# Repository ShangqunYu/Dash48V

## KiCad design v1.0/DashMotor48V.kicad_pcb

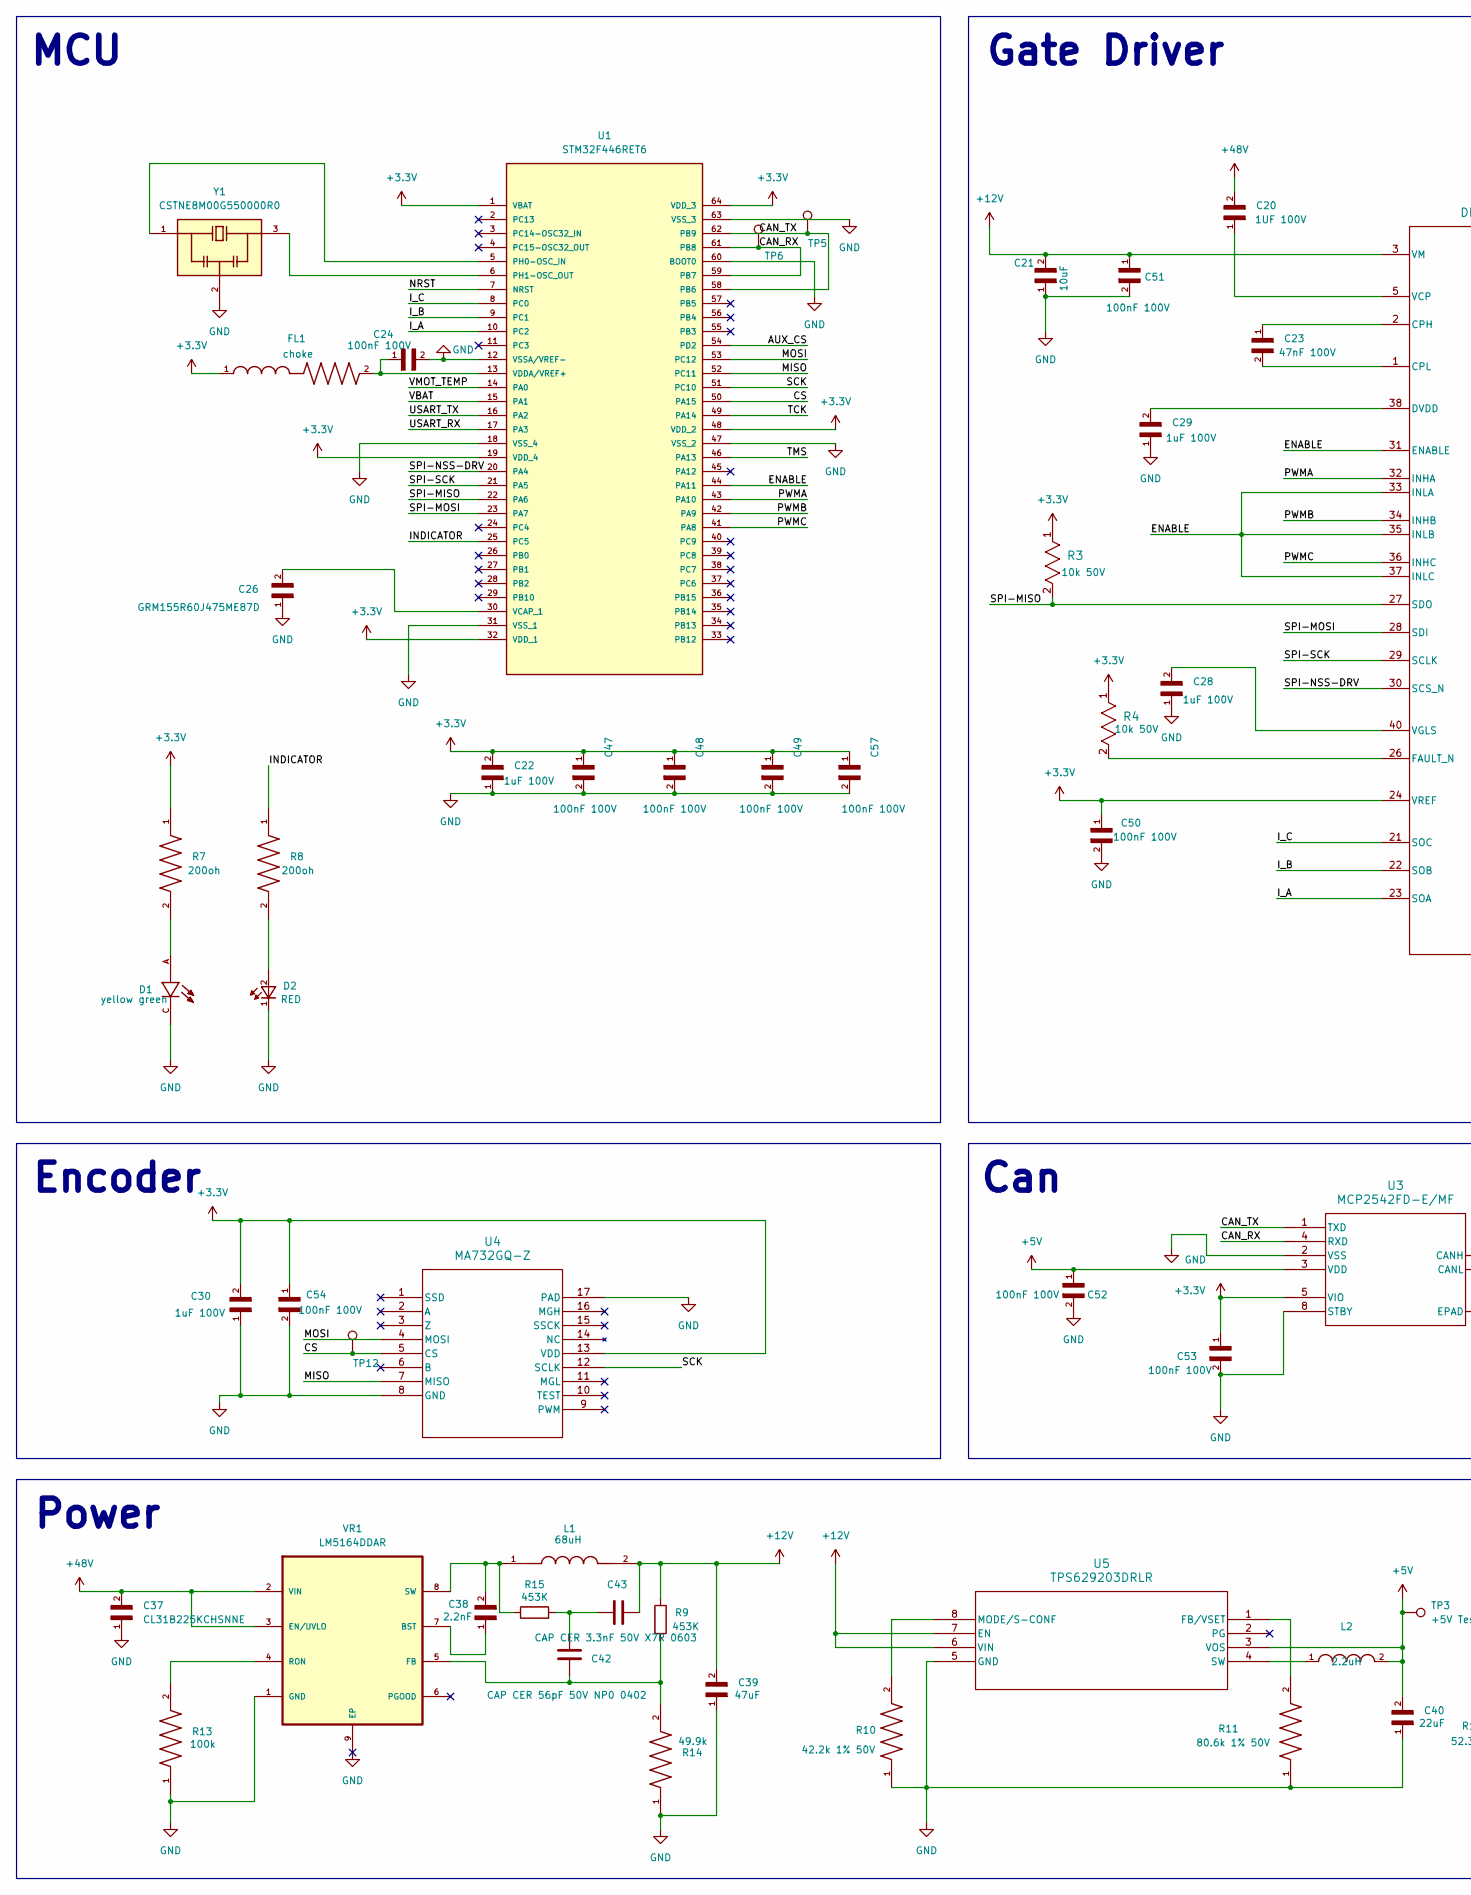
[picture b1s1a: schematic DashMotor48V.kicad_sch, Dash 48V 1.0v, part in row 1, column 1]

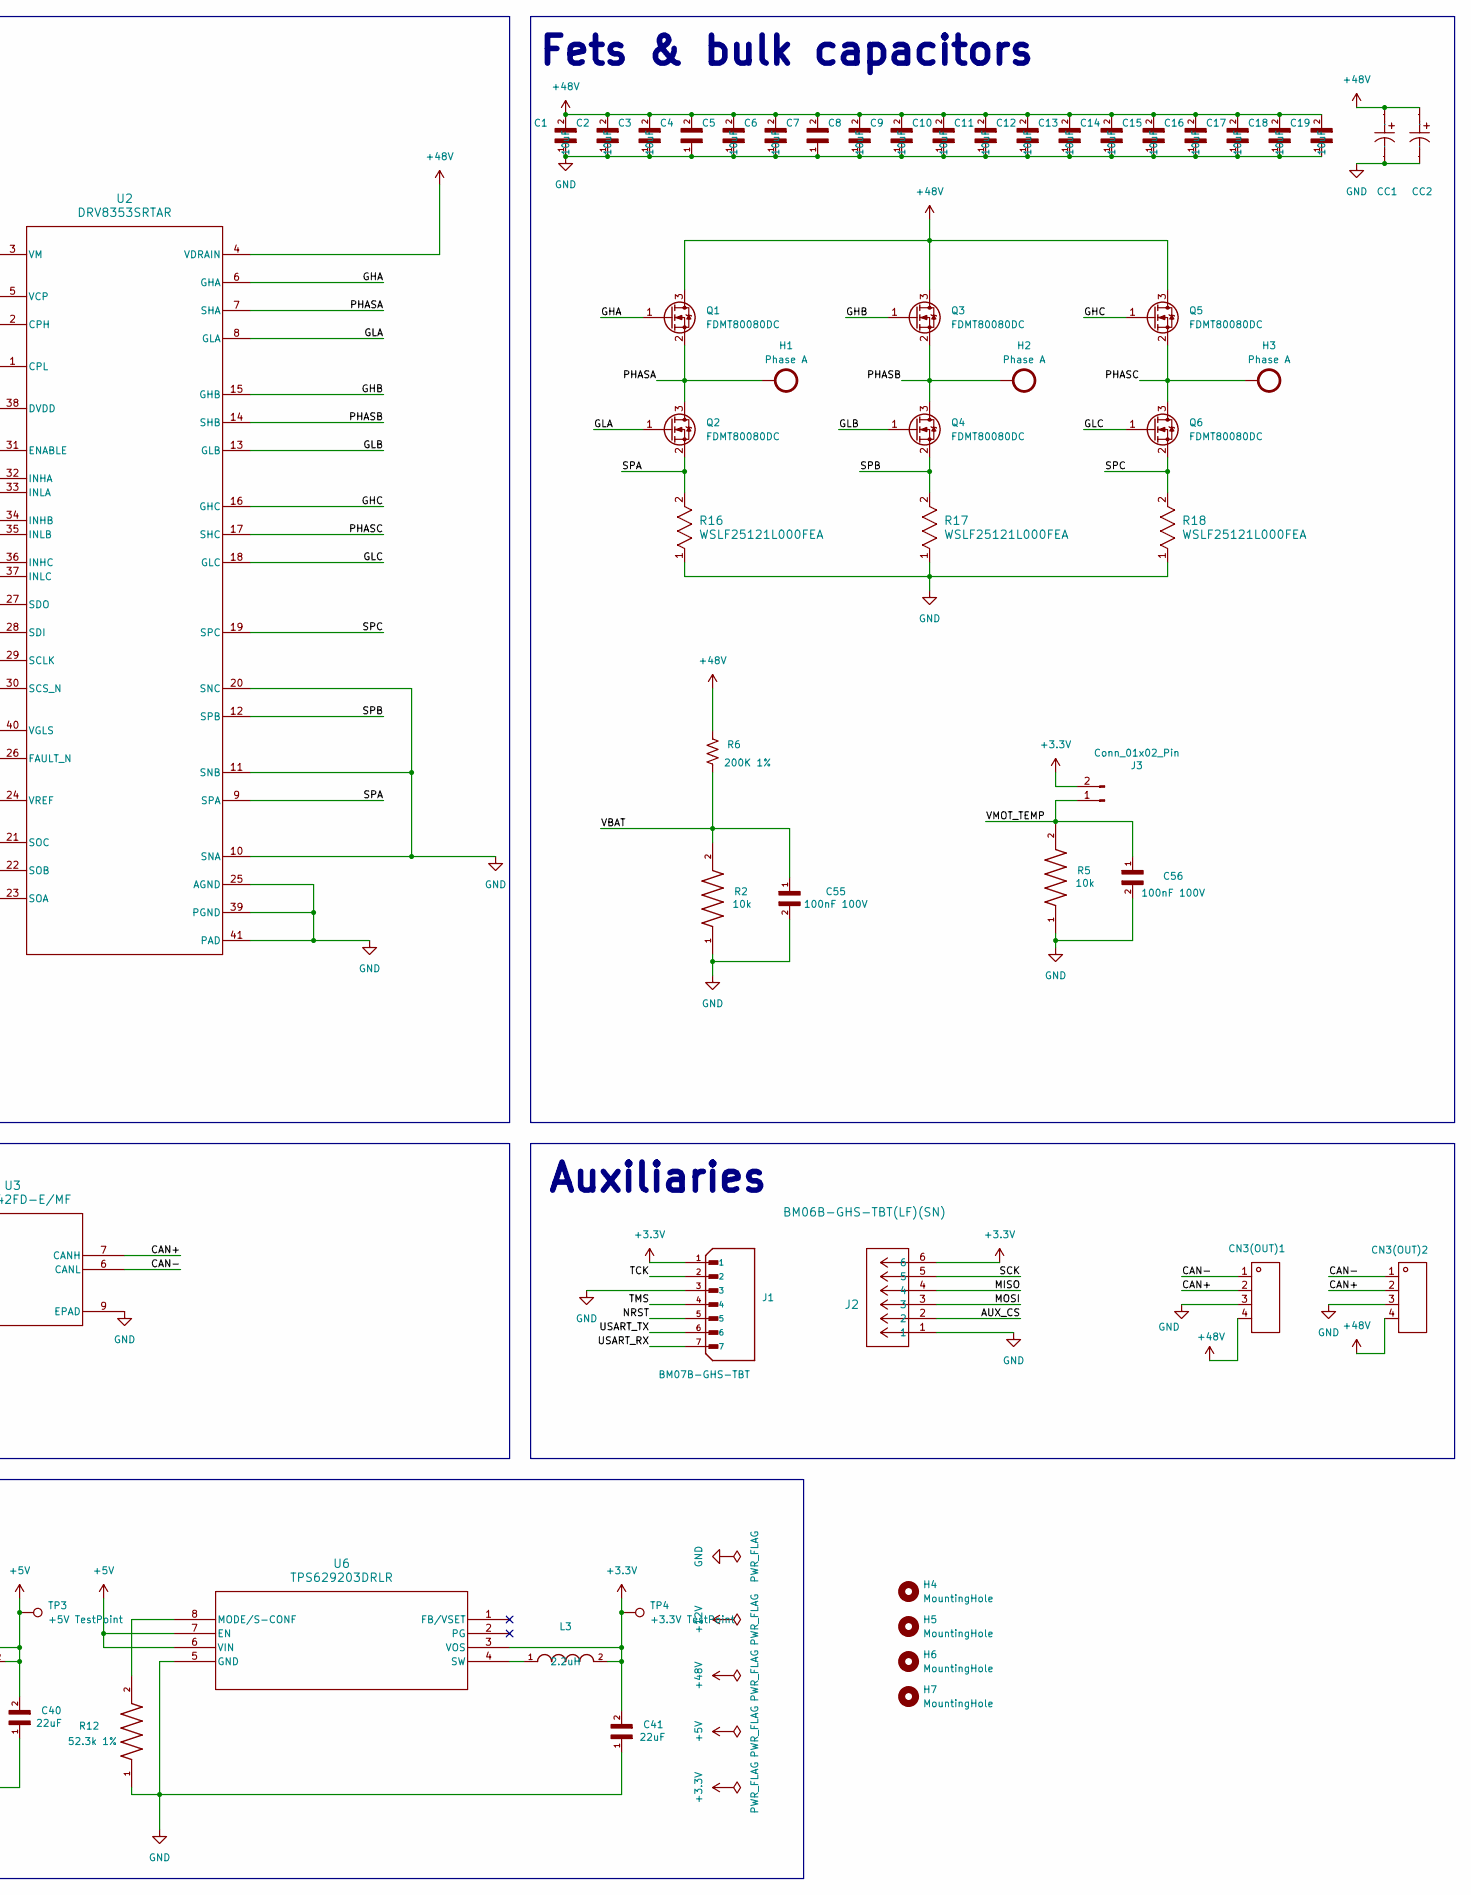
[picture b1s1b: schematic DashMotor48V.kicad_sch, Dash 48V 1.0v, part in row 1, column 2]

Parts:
C1, C2, C3, C4, C5, C6, C7, C8, C9, C10, C11, C12, C13, C14, C15, C16, C17, C18, C19, C21: GRM32EC72A106KE05L
C20: CL31B105KCHNNNE
C22, C28, C29, C30: GRM21BC72A105KE01L
C23: CC0603KRX7R0BB473
C24, C47, C48, C49, C50, C51, C52, C53, C54, C55, C56, C57: CL10B104KC8NNNC
C26: GRM155R60J475ME87D
C37: CL31B225KCHSNNE
C38: CL10B222KB8NNNC
C39: GRM31CR61E476ME44L
C40, C41: GRM32ER71E226KE15L
C42: CC0402JRNPO9BN560; RC0402FR_0752K3L
C43: CL10B332KB8NNNC; CC0603JRX7R9BB104; JLCpart C1613
CC1, CC2: EFVH100ADA101M10C0; FOLLON EFVH100ADA101M10C0; Manufacturer Part EFVH100ADA101M10C0; LCSC Part Name 100uF ±20% 100V
CN3(OUT)1, CN3(OUT)2: XT30(2+2)PB-M.G.B; Manufacturer Part XT30(2+2)PB-M.G.B
D1: LTST-C190KGKT
D2: LTST-C191KRKT; LTST_C191KRKT
FL1: BLM18AG601SN1D
H1, H2, H3: Phase A; Pad_Square_Vias_6.5x6.5mm
H4, H5, H6, H7: MountingHole; MountingHole_2.2mm_M2_Pad
J1: BM07B-GHS-TBT; JST_BM07B-GHS-TBT; PARTREV NA
J2: BM06B-GHS-TBT(LF)(SN); BM06B-GHS-TBT
J3: Conn_01x02_Pin; PinHeader_1x02_P2.54mm_Vertical
L1: VLS5045EX-680M; VLS5045EX_680M; PARTREV N/A
L2, L3: DFE252012PD-2R2M=P2; DFE252012PD_2R2M_P2
Q1, Q2, Q3, Q4, Q5, Q6: FDMT80080DC; FDMT80040DC_compact
R2, R5: RT0402DRE0710KL
R3, R4: RC0402FR-0710KL; RC0402FR_0710KL
R6: RT0603DRD07200KL; YAGEO RC0603FR-07200KL
R7, R8: RC0402JR-07200RL
R9, R15: ARG03BTC4533; RT0603BRD07448KL
R10: RC0402FR-0742K2L; RC0402FR_0742K2L
R11: RC0402FR-0780K6L; RC0402FR_0780K6L
R12: RC0402FR-0752K3L; RC0402FR_0752K3L
R13: RC0805FR-07100KL; RC0805FR_07100KL
R14: RT0603BRD0749K9L
R16, R17, R18: WSLF25121L000FEA
TP3: +5V TestPoint; TestPoint_Pad_D1.0mm
TP4: +3.3V TestPoint; TestPoint_Pad_D1.0mm
TP5, TP6: TP_Can_tx; TestPoint_Pad_D1.0mm
TP12: TP_CS; TestPoint_Pad_D1.0mm
U1: STM32F446RET6; STM32F446RCT6
U2: DRV8353SRTAR
U3: MCP2542FD-E/MF; MCP2542FD_E_MF
U4: MA732GQ-Z
U5, U6: TPS629203DRLR
VR1: LM5164DDAR
Y1: CSTNE8M00G550000R0

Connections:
+3.3V: C22.2, C30.2, C41.2, C47.1, C48.1, C49.1, C50.1, C53.1, C54.1, C57.1, FL1.1, J1.1, J2.6, J3.2, L3.2, R3.1, R4.1, R7.1, TP4.1 (1_1), U1.1 (VBAT), U1.19 (VDD_4), U1.32 (VDD_1), U1.48 (VDD_2), U1.64 (VDD_3), U2.24 (VREF), U3.5 (VIO), U4.13 (VDD), U6.3 (VOS)
+5V: C40.2, C52.1, L2.2, TP3.1 (1_1), U3.3 (VDD), U5.3 (VOS), U6.6 (VIN), U6.7 (EN)
+12V: C21.2, C39.2, C43.2, C51.1, L1.2, R9.1, U2.3 (VM), U5.6 (VIN), U5.7 (EN)
+48V: C1.2, C2.2, C3.2, C4.2, C5.2, C6.2, C7.2, C8.2, C9.2, C10.2, C11.2, C12.2, C13.2, C14.2, C15.2, C16.2, C17.2, C18.2, C19.2, C20.2, C37.2, CC1.1, CC2.1, CN3(OUT)1.4, CN3(OUT)2.4, Q1.3 (D), Q3.3 (D), Q5.3 (D), R6.1, U2.4 (VDRAIN), VR1.2 (VIN), VR1.3 (EN/UVLO)
/AUX_CS: J2.2, U1.54 (PD2)
/CAN+: CN3(OUT)1.2, CN3(OUT)2.2, U3.7 (CANH)
/CAN-: CN3(OUT)1.1, CN3(OUT)2.1, U3.6 (CANL)
/CAN_RX: TP6.1 (1_1), U1.59 (PB7), U1.61 (PB8), U3.4 (RXD)
/CAN_TX: TP5.1 (1_1), U1.58 (PB6), U1.62 (PB9), U3.1 (TXD)
/CS: TP12.1 (1_1), U1.50 (PA15), U4.5 (CS)
/ENABLE: U1.44 (PA11), U2.31 (ENABLE), U2.33 (INLA), U2.35 (INLB), U2.37 (INLC)
/GHA: Q1.1 (G), U2.6 (GHA)
/GHB: Q3.1 (G), U2.15 (GHB)
/GHC: Q5.1 (G), U2.16 (GHC)
/GLA: Q2.1 (G), U2.8 (GLA)
/GLB: Q4.1 (G), U2.13 (GLB)
/GLC: Q6.1 (G), U2.18 (GLC)
/INDICATOR: R8.1, U1.25 (PC5)
/I_A: U1.10 (PC2), U2.23 (SOA)
/I_B: U1.9 (PC1), U2.22 (SOB)
/I_C: U1.8 (PC0), U2.21 (SOC)
/MISO: J2.4, U1.52 (PC11), U4.7 (MISO)
/MOSI: J2.3, U1.53 (PC12), U4.4 (MOSI)
/NRST: J1.5, U1.7 (NRST)
/PHASA: H1.1 (1_1), Q1.2 (S), Q2.3 (D), U2.7 (SHA)
/PHASB: H2.1 (1_1), Q3.2 (S), Q4.3 (D), U2.14 (SHB)
/PHASC: H3.1 (1_1), Q5.2 (S), Q6.3 (D), U2.17 (SHC)
/PWMA: U1.43 (PA10), U2.32 (INHA)
/PWMB: U1.42 (PA9), U2.34 (INHB)
/PWMC: U1.41 (PA8), U2.36 (INHC)
/SCK: J2.5, U1.51 (PC10), U4.12 (SCLK)
/SPA: Q2.2 (S), R16.2, U2.9 (SPA)
/SPB: Q4.2 (S), R17.2, U2.12 (SPB)
/SPC: Q6.2 (S), R18.2, U2.19 (SPC)
/SPI-MISO: R3.2, U1.22 (PA6), U2.27 (SDO)
/SPI-MOSI: U1.23 (PA7), U2.28 (SDI)
/SPI-NSS-DRV: U1.20 (PA4), U2.30 (SCS_N)
/SPI-SCK: U1.21 (PA5), U2.29 (SCLK)
/TCK: J1.2, U1.49 (PA14)
/TMS: J1.4, U1.46 (PA13)
/USART_RX: J1.7, U1.17 (PA3)
/USART_TX: J1.6, U1.16 (PA2)
/VBAT: C55.1, R2.2, R6.2, U1.15 (PA1)
/VMOT_TEMP: C56.1, J3.1, R5.2, U1.14 (PA0)
GND: C1.1, C2.1, C3.1, C4.1, C5.1, C6.1, C7.1, C8.1, C9.1, C10.1, C11.1, C12.1, C13.1, C14.1, C15.1, C16.1, C17.1, C18.1, C19.1, C21.1, C22.1, C24.2, C26.1, C28.1, C29.1, C30.1, C37.1, C39.1, C40.1, C41.1, C47.2, C48.2, C49.2, C50.2, C51.2, C52.2, C53.2, C54.2, C55.2, C56.2, C57.2, CC1.2, CC2.2, CN3(OUT)1.3, CN3(OUT)2.3, D1.C, D2.1, J1.3, J2.1, R2.1, R5.1, R10.1, R11.1, R12.1, R13.1, R14.1, R16.1, R17.1, R18.1, U1.12 (VSSA/VREF-), U1.18 (VSS_4), U1.31 (VSS_1), U1.47 (VSS_2), U1.60 (BOOT0), U1.63 (VSS_3), U2.10 (SNA), U2.11 (SNB), U2.20 (SNC), U2.25 (AGND), U2.39 (PGND), U2.41 (PAD), U3.2 (VSS), U3.8 (STBY), U3.9 (EPAD), U4.8 (GND), U4.17 (PAD), U5.5 (GND), U6.5 (GND), VR1.1 (GND), VR1.9 (EP), Y1.2
unnamed: C42.1, C43.1, R15.2
unnamed: D1.A, R7.2
unnamed: D2.2, R8.2
unnamed: U1.5 (PH0-OSC_IN), Y1.1
unnamed: U1.6 (PH1-OSC_OUT), Y1.3
unnamed: C26.2, U1.30 (VCAP_1)
unnamed: C24.1, FL1.2, U1.13 (VDDA/VREF+)
unnamed: C23.1, U2.2 (CPH)
unnamed: C23.2, U2.1 (CPL)
unnamed: C29.2, U2.38 (DVDD)
unnamed: R4.2, U2.26 (FAULT_N)
unnamed: C20.1, U2.5 (VCP)
unnamed: C28.2, U2.40 (VGLS)
unnamed: R11.2, U5.1 (FB/VSET)
unnamed: R10.2, U5.8 (MODE/S-CONF)
unnamed: L2.1, U5.4 (SW)
unnamed: R12.2, U6.8 (MODE/S-CONF)
unnamed: L3.1, U6.4 (SW)
unnamed: C38.1, VR1.7 (BST)
unnamed: C42.2, R9.2, R14.2, VR1.5 (FB)
unnamed: R13.2, VR1.4 (RON)
unnamed: C38.2, L1.1, R15.1, VR1.8 (SW)

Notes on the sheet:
MCU
Auxiliaries
Gate Driver
Can
Encoder
Fets & bulk capacitors
Power

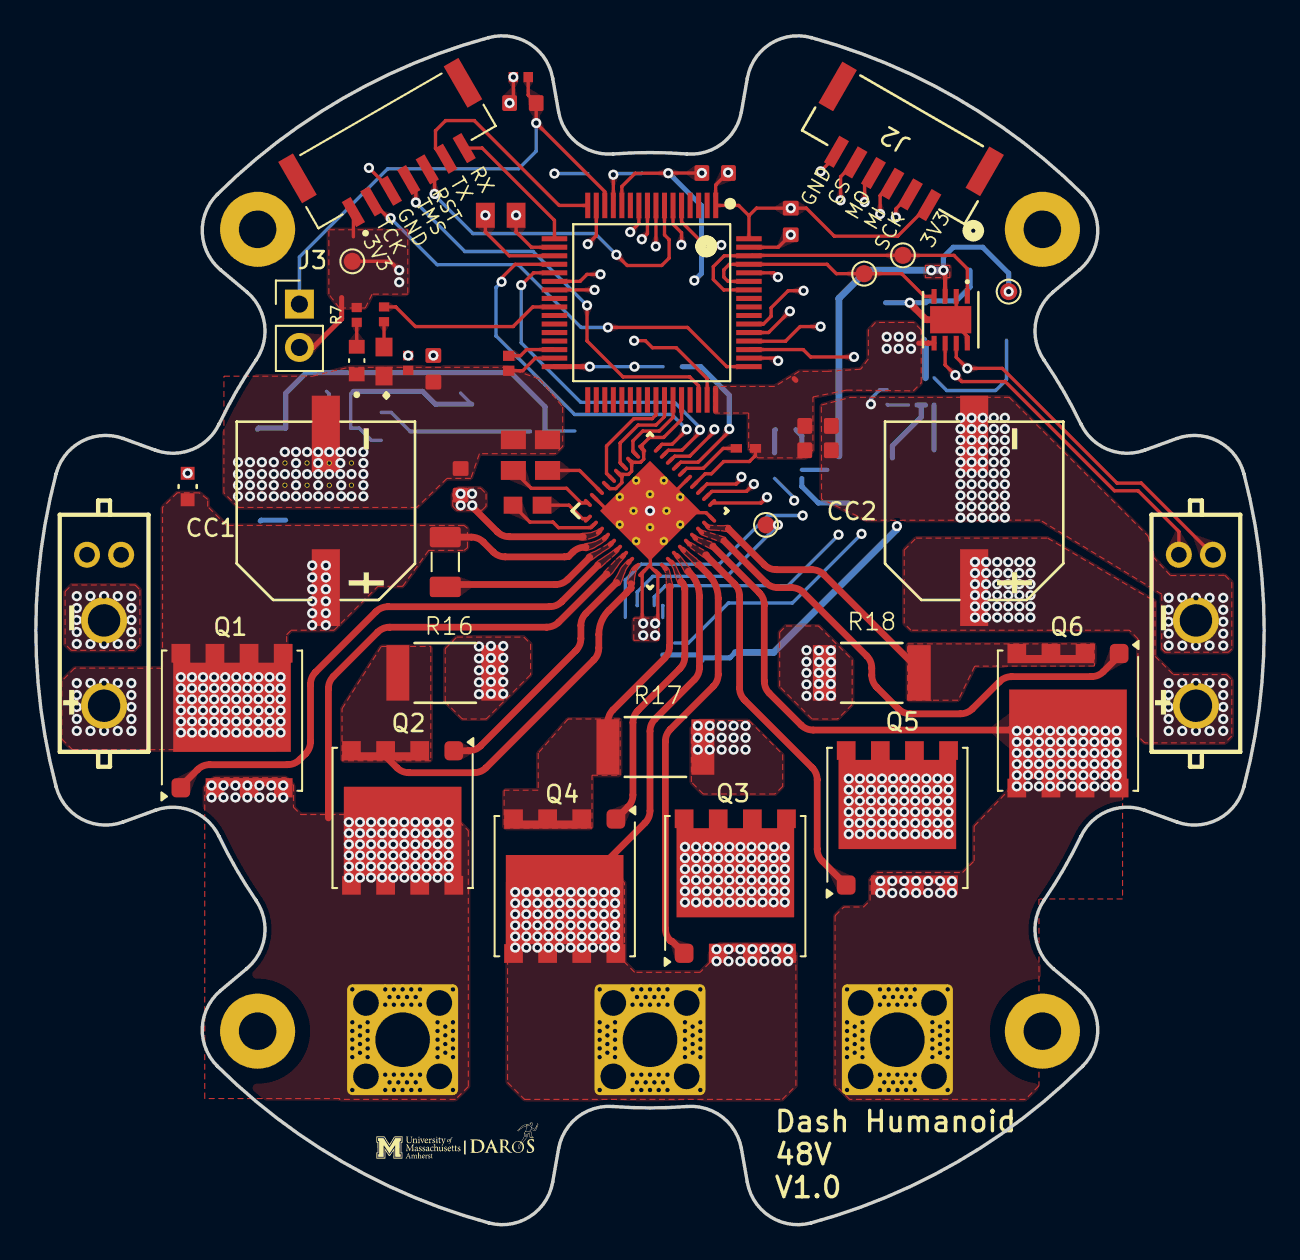
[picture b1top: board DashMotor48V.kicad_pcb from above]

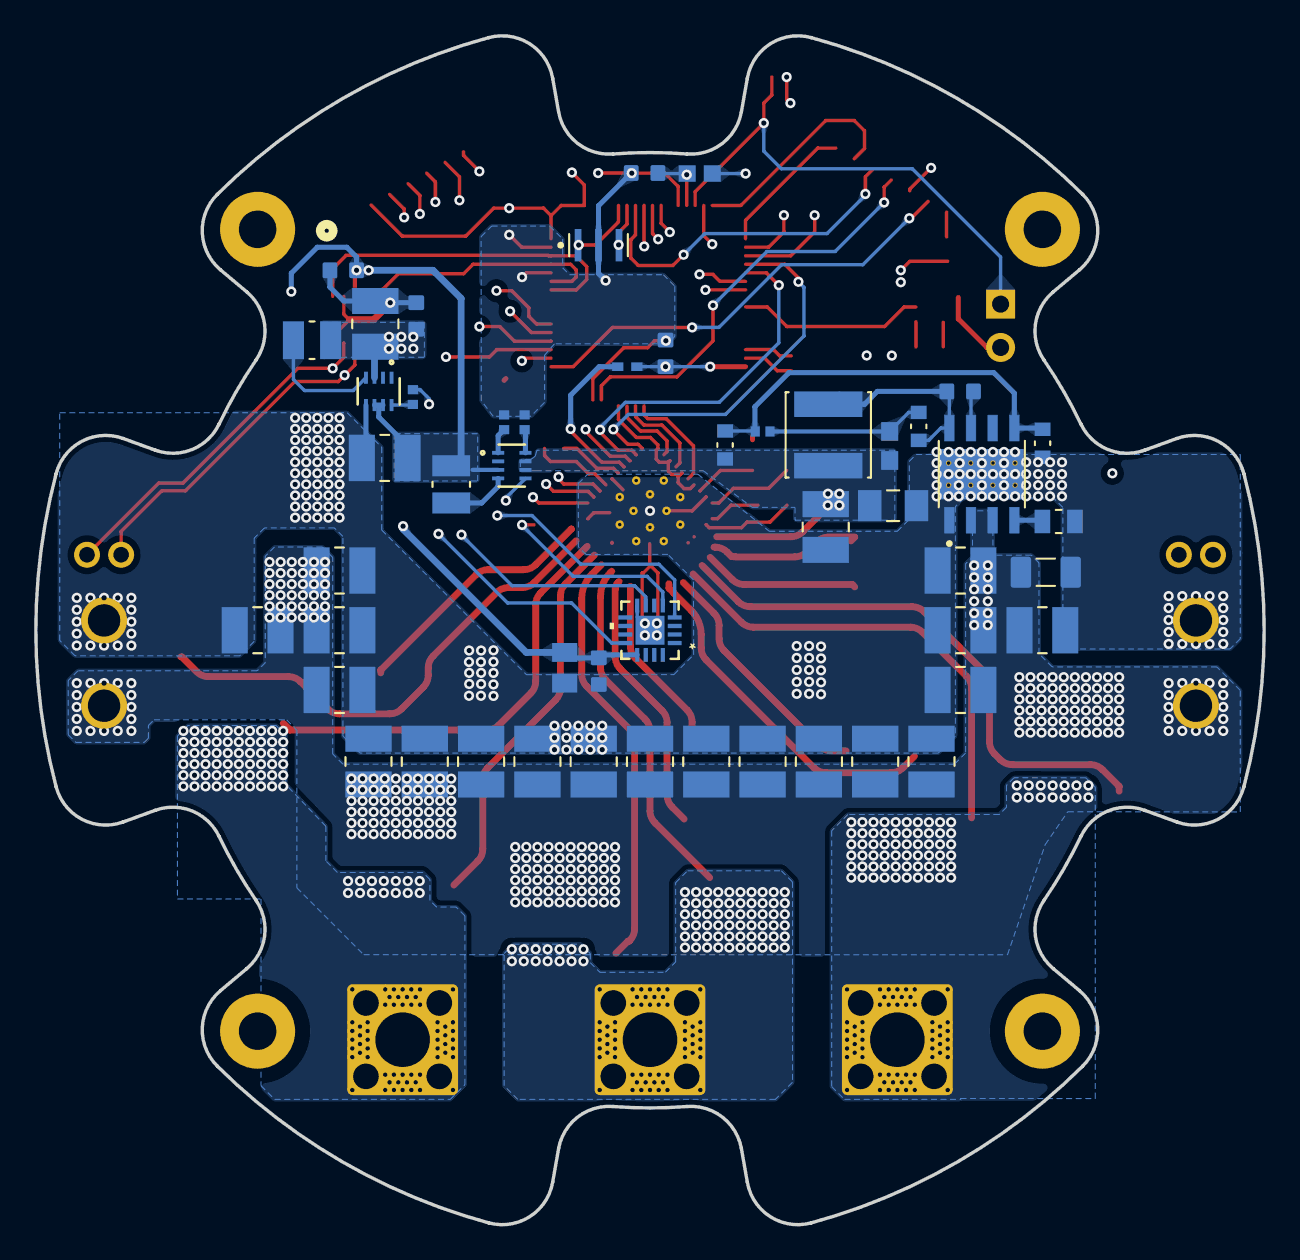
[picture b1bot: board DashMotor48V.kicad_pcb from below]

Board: 6 copper layers, 72.0 x 69.7 mm, 102 parts (50 on the bottom side), 67 nets.

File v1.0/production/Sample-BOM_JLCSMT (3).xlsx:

Comment | Designator | Footprint | JLCPCB Part #（optional）
GRM32EC72A106KE05L | C1, C2, C3, C4, C5, C6, C7, C8, C9, C10, C11, C12, C13, C14, C15, C16, C17, C18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 | GRM32EC72A106KE05L | GRM32EC72A106KE05L
CL31B105KCHNNNE | C20 | CL31B105KCHNNNE | CL31B105KCHNNNE
GRM21BC72A105KE01L | C22, C28, C29, C30 | GRM21BC72A105KE01L | GRM21BC72A105KE01L
CC0603KRX7R0BB473 | C23 | CC0603KRX7R0BB473 | CC0603KRX7R0BB473
CL10B104KC8NNNC | C24, C47, C48, C49, C50, C51, C52, C53, C54, C55, C56, C57 | CL10B104KC8NNNC | CL10B104KC8NNNC
GRM155R60J475ME87D | C26 | GRM155R60J475ME87D | GRM155R60J475ME87D
CL31B225KCHSNNE | C37 | CL31B225KCHSNNE | CL31B225KCHSNNE
CL10B222KB8NNNC | C38 | CL10B222KB8NNNC | CL10B222KB8NNNC
GRM31CR61E476ME44L | C39 | GRM31CR61E476ME44L | GRM31CR61E476ME44L
GRM32ER71E226KE15L | C40, C41 | GRM32ER71E226KE15L | GRM32ER71E226KE15L
CC0402JRNPO9BN560 | C42 | CC0402JRNPO9BN560 | CC0402JRNPO9BN560
CL10B332KB8NNNC | C43 | CL10B332KB8NNNC | CL10B332KB8NNNC
EFVH100ADA101M10C0 | CC1, CC2 | EFVH100ADA101M10C0 | EFVH100ADA101M10C0
XT30(2+2)PB-M.G.B | CN3(OUT)1, CN3(OUT)2 | XT30(2+2)PB-M.G.B | XT30(2+2)PB-M.G.B
LTST-C190KGKT | D1 | LTST-C190KGKT | LTST-C190KGKT
LTST-C191KRKT | D2 | LTST-C191KRKT | LTST-C191KRKT
BLM18AG601SN1D | FL1 | BLM18AG601SN1D | BLM18AG601SN1D
BM07B-GHS-TBT | J1 | BM07B-GHS-TBT | BM07B-GHS-TBT
BM06B-GHS-TBT(LF)(SN) | J2 | BM06B-GHS-TBT(LF)(SN) | BM06B-GHS-TBT(LF)(SN)
Conn_01x02_Pin | J3 | Conn_01x02_Pin | Conn_01x02_Pin
VLS5045EX-680M | L1 | VLS5045EX-680M | VLS5045EX-680M
DFE252012PD-2R2M=P2 | L2, L3 | DFE252012PD-2R2M=P2 | DFE252012PD-2R2M=P2
FDMT80080DC | Q1, Q2, Q3, Q4, Q5, Q6 | FDMT80080DC | FDMT80080DC
RT0402DRE0710KL | R2, R5 | RT0402DRE0710KL | RT0402DRE0710KL
RC0402FR-0710KL | R3, R4 | RC0402FR-0710KL | RC0402FR-0710KL
RT0603DRD07200KL | R6 | RT0603DRD07200KL | RT0603DRD07200KL
RC0402JR-07200RL | R7, R8 | RC0402JR-07200RL | RC0402JR-07200RL
ARG03BTC4533 | R9, R15 | ARG03BTC4533 | ARG03BTC4533
RC0402FR-0742K2L | R10 | RC0402FR-0742K2L | RC0402FR-0742K2L
RC0402FR-0780K6L | R11 | RC0402FR-0780K6L | RC0402FR-0780K6L
RC0402FR-0752K3L | R12 | RC0402FR-0752K3L | RC0402FR-0752K3L
RC0805FR-07100KL | R13 | RC0805FR-07100KL | RC0805FR-07100KL
RT0603BRD0749K9L | R14 | RT0603BRD0749K9L | RT0603BRD0749K9L
WSLF25121L000FEA | R16, R17, R18 | WSLF25121L000FEA | WSLF25121L000FEA
+5V TestPoint | TP3 | +5V TestPoint | +5V TestPoint
+3.3V TestPoint | TP4 | +3.3V TestPoint | +3.3V TestPoint
TP_Can_tx | TP5, TP6 | TP_Can_tx | TP_Can_tx
TP_CS | TP12 | TP_CS | TP_CS
STM32F446RET6 | U1 | STM32F446RET6 | STM32F446RET6
DRV8353SRTAR | U2 | DRV8353SRTAR | DRV8353SRTAR
MCP2542FD-E/MF | U3 | MCP2542FD-E/MF | MCP2542FD-E/MF
MA732GQ-Z | U4 | MA732GQ-Z | MA732GQ-Z
TPS629203DRLR | U5, U6 | TPS629203DRLR | TPS629203DRLR
LM5164DDAR | VR1 | LM5164DDAR | LM5164DDAR
CSTNE8M00G550000R0 | Y1 | CSTNE8M00G550000R0 | CSTNE8M00G550000R0

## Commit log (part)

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2025-12-01 Add README for Dash48V motor controller board
2025-12-01 first commit from laptop
2025-12-01 include the mosfet
2025-12-02 get can chip done
2025-12-02 finishing the routing
2025-12-02 start on routing
2025-12-03 finish schematic
2025-12-03 figure out the schematic
2025-12-03 back up work on footprint
2025-12-03 get the footprint for the bigger motor
2025-12-03 start placing
2025-12-03 push
2025-12-04 put onto the board
2025-12-05 have a good layout
2025-12-07 1 draft
2025-12-07 1st draft
2025-12-08 power distribution + signal integrity improvements
2025-12-08 will start 2nd version
2025-12-10 added Square Vias from Moteus
2025-12-11 formalize footprint and port
2025-12-11 keep working on the 2nd version
2025-12-11 keep working on 2nd version
2025-12-12 work on 2ndraft
2025-12-13 no error for the 2nd draft
2025-12-14 minor tweak
2025-12-15 change color and stuff
2025-12-16 need to add testing probe
2025-12-16 change a smaller shunt resistor and add more ground vias
2025-12-16 increase ground and 48v copper pour on layer six
2025-12-17 Added TestPoints for Power
2025-12-17 Added TestPoints for poer
2025-12-17 added more testing point, replace obsolete part, final review
2025-12-17 noticed they have stm32f446ret, will use that
2025-12-17 clean up
2025-12-19 version sent to production
2026-04-15 make different version
2026-04-17 push to desktop
2026-04-17 keep working on v05
2026-04-20 back up
2026-04-20 push to the repo
2026-04-20 update pcb
2026-04-20 upload again
2026-04-20 work on routing
2026-04-22 backup
2026-04-24 keep routing
2026-04-27 finish first draft
2026-04-27 fix canrx tx pin place
2026-04-27 keep tuning few things
2026-04-29 adding more copper to the board
2026-04-30 keep finishing it
2026-05-01 fine tune
2026-05-01 doing fine touch for the routing, almost done
2026-05-02 finetuning
2026-06-30 start working on version 1
